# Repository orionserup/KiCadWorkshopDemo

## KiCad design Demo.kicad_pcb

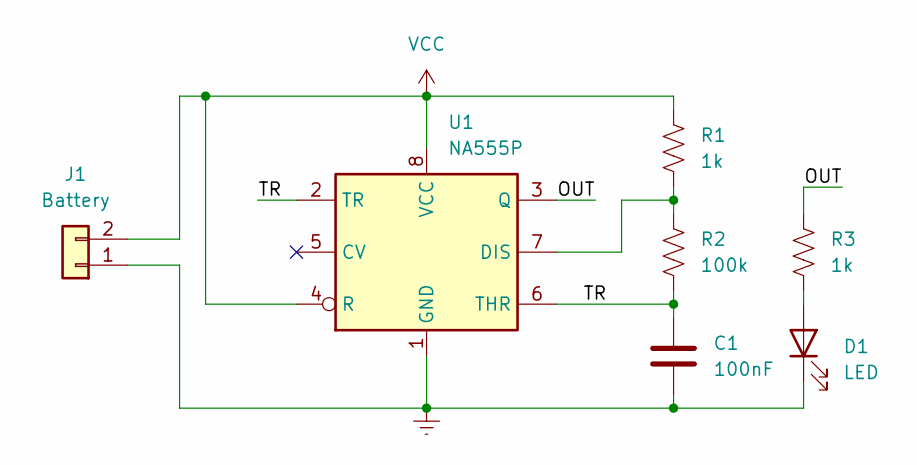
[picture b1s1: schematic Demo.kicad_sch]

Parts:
C1: 100nF; CP_Radial_D4.0mm_P2.00mm
D1: LED; LED_D3.0mm
J1: Battery; PinSocket_1x02_P2.54mm_Vertical
R1, R3: 1k; R_Axial_DIN0207_L6.3mm_D2.5mm_P10.16mm_Horizontal
R2: 100k; R_Axial_DIN0207_L6.3mm_D2.5mm_P10.16mm_Horizontal
U1: NA555P; DIP-8_W7.62mm

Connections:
/OUT: R3.1, U1.3 (Q)
/TR: C1.1, R2.2, U1.2 (TR), U1.6 (THR)
Earth: C1.2, D1.1 (K), J1.1, U1.1 (GND)
unnamed: D1.2 (A), R3.2
unnamed: R1.2, R2.1, U1.7 (DIS)
VCC: J1.2, R1.1, U1.4 (R), U1.8 (VCC)

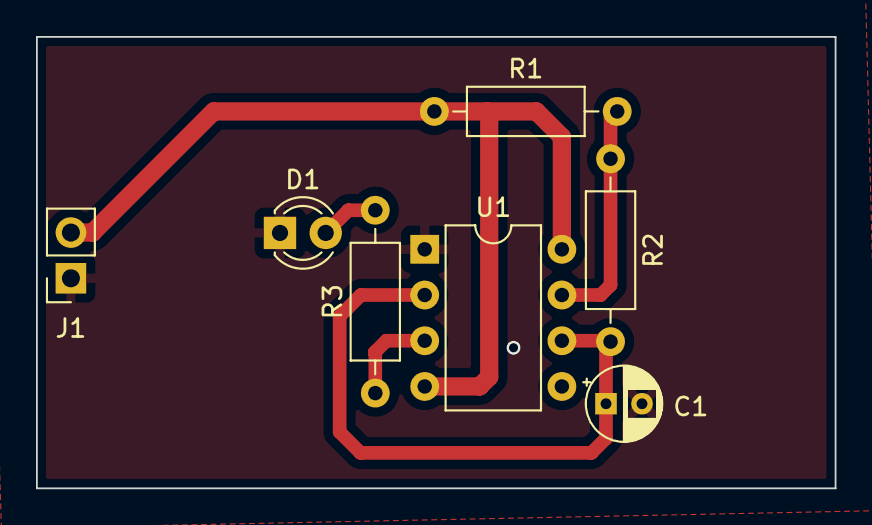
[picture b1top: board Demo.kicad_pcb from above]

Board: 2 copper layers, 44.4 x 25.1 mm, 7 parts (0 on the bottom side), 6 nets.

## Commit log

2022-12-15 added PCB files
